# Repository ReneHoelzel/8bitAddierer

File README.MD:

# 8bit Addierer

Das Projekt wurde in Zusammenarbeit mit dem Zuseum in Bautzen entwickelt und soll Schülern und interessierten die Rechenweise eine Computers anhand eines Bytes (=8bit) veranschaulichen. 

## Aufbau

Im unteren Bereich befindet sich ein Arduino Nano V3 als Steuereinheit sowie 8x Doppelpins an die je ein Taster angeschlossen werden kann. Ein Anschlus für den neunten Taster (Erläterung siehe Funktion) befindet sich unter dem Arduino.<br/>

## Funktion

Mit den 8 Tastern kann die dazugehörige 7-Segment Anzeige/rote LED jeweils ein- oder ausgeschalten werden. Je nachdem welche "Bits" eingeschalten sind wird oben in der 3-stelligen Anzeige der entsprechende Wert als Ganzzahl (Byte) ausgegeben.

Zum Beispiel: 0 0 0 0 1 0 0 1 entspricht dem Wert 9.

Mit dem neunten Taster kann das Ergebnis "ausgeblendet" werden (es wird der Wert 999 angezeigt). Dies kann verwendet werden, um einen Wert einzustellen und die Schüler herausfinden zu lassen welcher Byte-Wert sich dahinter verbirgt.

<br/>

<span style="color:red;">Die Verwendung erfolgt auf eigene Gefahr.<span/>

Zum Arduino Programm geht es [hier](https://github.com/ReneHoelzel/8bitAddierer/tree/main/Program).

Es gibt aktuell 2 Board Revisionen:

- [Revision A](8BitZahlAnzeige_RevA/README.MD)

- [Revision B](8BitZahlAnzeige_RevB/README.MD)

Der Unterschied zu beiden Versionen ist, dass bei Revision B die 8x 7-Segment Anzeige und der MAX7219 Steuerchip die Positionen getauscht haben.

## ToDo

- Gehäuse entwerfen

- Animation der 3-stelligen Anzeige, wenn der neunte Taster gedrückt ist.

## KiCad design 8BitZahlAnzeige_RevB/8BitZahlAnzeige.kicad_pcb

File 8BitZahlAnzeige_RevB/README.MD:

# 8bit Addierer

##### Revision B

[Zurück zur Startseite](https://github.com/ReneHoelzel/8bitAddierer/tree/main)

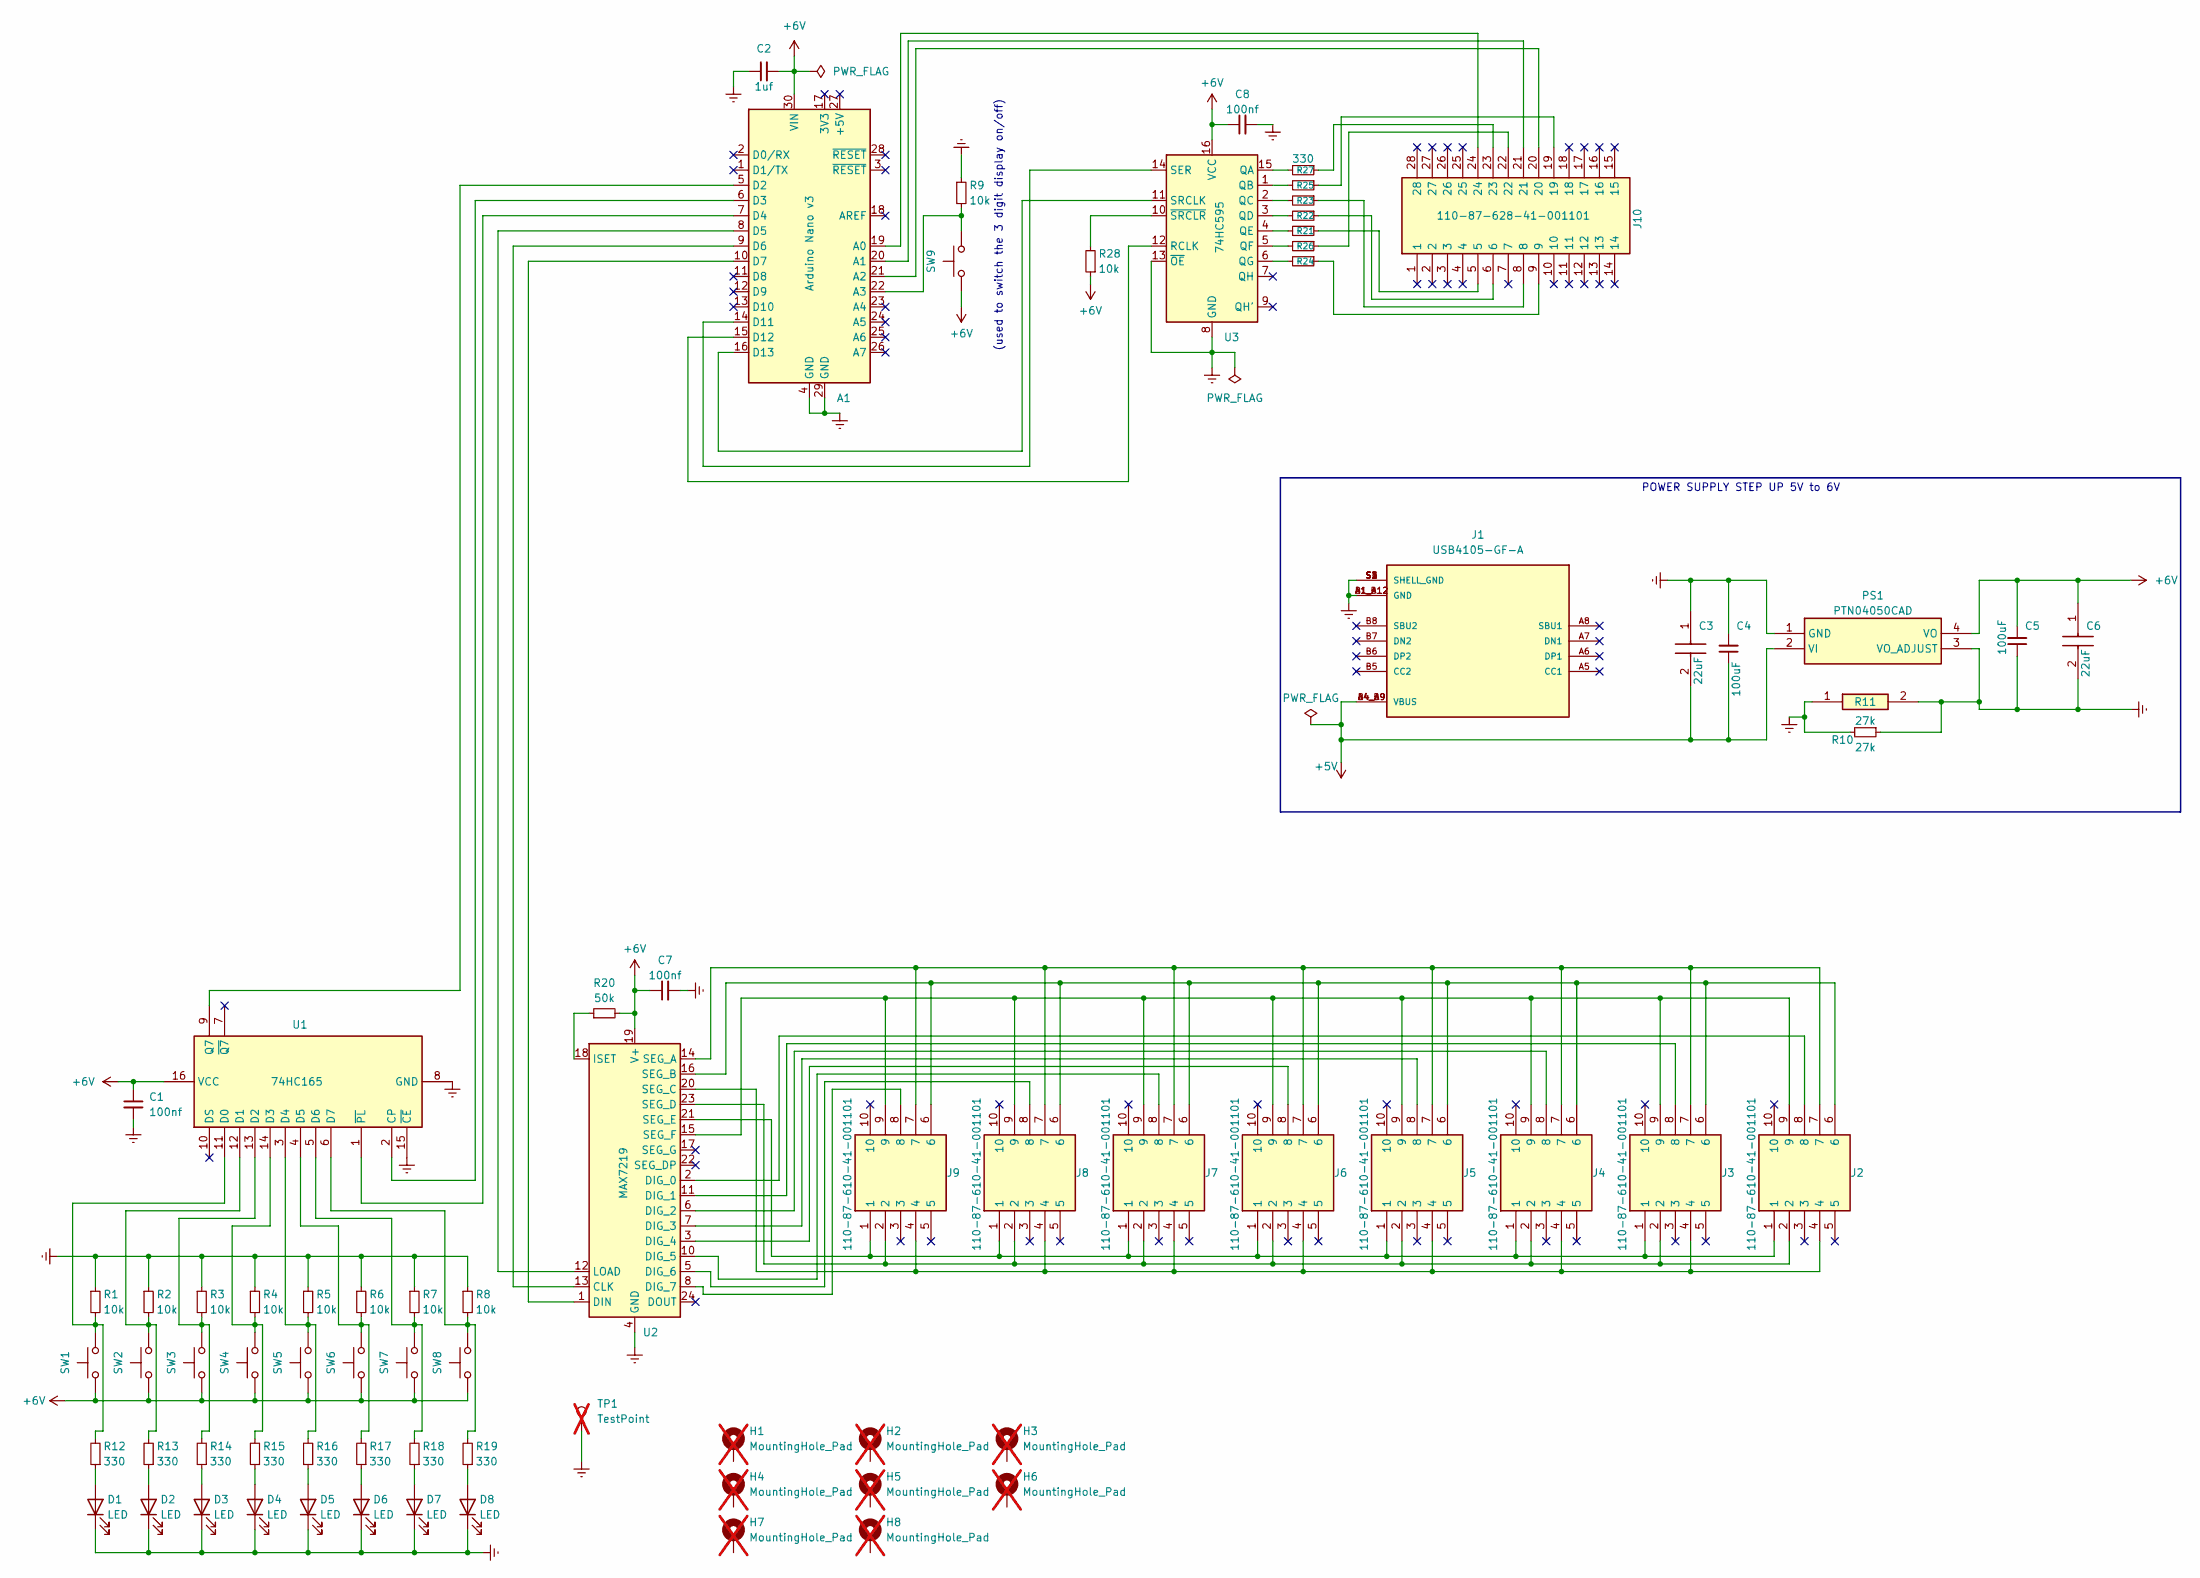
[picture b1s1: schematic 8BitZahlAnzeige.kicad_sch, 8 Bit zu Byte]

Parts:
A1: Arduino Nano v3; Arduino_Nano
C1, C7, C8: 100nf; C_Disc_D5.0mm_W2.5mm_P2.50mm
C2: 1uf; CP_Radial_D4.0mm_P2.00mm
C3, C6: 22uF; C4532_Commercial; Mouser Part Number 810-C4532X7R1C226M10
C4, C5: 100uF; CP_Radial_D5.0mm_P2.50mm
D1, D2, D3, D4, D5, D6, D7, D8: LED; LED_D5.0mm
H1, H2, H3, H4, H5, H6, H7, H8: MountingHole_Pad; MountingHole_3.2mm_M3_DIN965_Pad; not fitted
J1: USB4105-GF-A; GCT_USB4105-GF-A; PARTREV A3
J2, J3, J4, J5, J6, J7, J8, J9: 110-87-610-41-001101; DIPS1524W50P254L1270H370Q10N; Mouser Part Number 437-1108761041001101
J10: 110-87-628-41-001101; DIP-28_W15.24mm_Socket; Mouser Part Number 437-1108762841001101
PS1: PTN04050CAD; PTN04050CAH; Manufacturer_Part_Number PTN04050CAD; Mouser Part Number 595-PTN04050CAD
R1, R2, R3, R4, R5, R6, R7, R8, R9, R28: 10k; R_Axial_DIN0207_L6.3mm_D2.5mm_P10.16mm_Horizontal
R10: 27k; R_Axial_DIN0207_L6.3mm_D2.5mm_P10.16mm_Horizontal
R11: 27k; R_0201_0603Metric; Mouser Part Number 660-RK73H1HTTC2702F
R12, R13, R14, R15, R16, R17, R18, R19, R21, R22, R23, R24, R25, R26, R27: 330; R_Axial_DIN0207_L6.3mm_D2.5mm_P10.16mm_Horizontal
R20: 50k; R_Axial_DIN0207_L6.3mm_D2.5mm_P10.16mm_Horizontal
SW1, SW2, SW3, SW4, SW5, SW6, SW7, SW8, SW9: SW_Push; PinHeader_1x02_P2.54mm_Vertical
TP1: TestPoint; TestPoint_Pad_2.0x2.0mm; not fitted
U1: 74HC165; DIP-16_W7.62mm_Socket
U2: MAX7219; DIP-24_W7.62mm_Socket
U3: 74HC595; DIP-16_W7.62mm_Socket

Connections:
+5V: C3.2, C4.1, J1.A4_B9 (VBUS), J1.B4_A9 (VBUS), PS1.2 (VI)
+6V: A1.30 (VIN), C1.1, C2.2, C5.2, C6.1, C7.1, C8.1, PS1.4 (VO), R20.2, R28.1, SW1.1, SW2.1, SW3.1, SW4.1, SW5.1, SW6.1, SW7.1, SW8.1, SW9.1, U1.16 (VCC), U2.19 (V+), U3.16 (VCC)
GNDREF: A1.4 (GND), A1.29 (GND), C1.2, C2.1, C3.1, C4.2, C5.1, C6.2, C7.2, C8.2, D1.1 (K), D2.1 (K), D3.1 (K), D4.1 (K), D5.1 (K), D6.1 (K), D7.1 (K), D8.1 (K), J1.A1_B12 (GND), J1.B1_A12 (GND), J1.S1 (SHELL_GND), J1.S2 (SHELL_GND), J1.S3 (SHELL_GND), J1.S4 (SHELL_GND), PS1.1 (GND), PS1.3 (VO_ADJUST), R1.1, R2.1, R3.1, R4.1, R5.1, R6.1, R7.1, R8.1, R9.1, R10.1, R10.2, R11.1, R11.2, TP1.1, U1.8 (GND), U1.15 (~CE), U2.4 (GND), U2.9 (GND), U3.8 (GND), U3.13 (~OE)
unnamed: A1.19 (A0), J10.24
unnamed: A1.20 (A1), J10.21
unnamed: A1.21 (A2), J10.20
unnamed: A1.22 (A3), R9.2, SW9.2
unnamed: A1.5 (D2), U1.9 (Q7)
unnamed: A1.6 (D3), U1.2 (CP)
unnamed: A1.7 (D4), U1.1 (~PL)
unnamed: A1.8 (D5), U2.12 (LOAD)
unnamed: A1.9 (D6), U2.13 (CLK)
unnamed: A1.10 (D7), U2.1 (DIN)
unnamed: A1.14 (D11), U3.14 (SER)
unnamed: A1.15 (D12), U3.12 (RCLK)
unnamed: A1.16 (D13), U3.11 (SRCLK)
unnamed: D1.2 (A), R12.1
unnamed: D2.2 (A), R13.1
unnamed: D3.2 (A), R14.1
unnamed: D4.2 (A), R15.1
unnamed: D5.2 (A), R16.1
unnamed: D6.2 (A), R17.1
unnamed: D7.2 (A), R18.1
unnamed: D8.2 (A), R19.1
unnamed: J10.5, R21.1
unnamed: J10.6, R22.1
unnamed: J10.8, R23.1
unnamed: J10.9, R24.1
unnamed: J10.19, R25.1
unnamed: J10.22, R26.1
unnamed: J10.23, R27.1
unnamed: R1.2, R12.2, SW1.2, U1.11 (D0)
unnamed: R2.2, R13.2, SW2.2, U1.12 (D1)
unnamed: R3.2, R14.2, SW3.2, U1.13 (D2)
unnamed: R4.2, R15.2, SW4.2, U1.14 (D3)
unnamed: R5.2, R16.2, SW5.2, U1.3 (D4)
unnamed: R6.2, R17.2, SW6.2, U1.4 (D5)
unnamed: R7.2, R18.2, SW7.2, U1.5 (D6)
unnamed: R8.2, R19.2, SW8.2, U1.6 (D7)
unnamed: J2.8, U2.2 (DIG_0)
unnamed: J3.8, U2.11 (DIG_1)
unnamed: J4.8, U2.6 (DIG_2)
unnamed: J5.8, U2.7 (DIG_3)
unnamed: J6.8, U2.3 (DIG_4)
unnamed: J7.8, U2.10 (DIG_5)
unnamed: J8.8, U2.5 (DIG_6)
unnamed: J9.8, U2.8 (DIG_7)
unnamed: R20.1, U2.18 (ISET)
unnamed: J2.7, J3.7, J4.7, J5.7, J6.7, J7.7, J8.7, J9.7, U2.14 (SEG_A)
unnamed: J2.6, J3.6, J4.6, J5.6, J6.6, J7.6, J8.6, J9.6, U2.16 (SEG_B)
unnamed: J2.4, J3.4, J4.4, J5.4, J6.4, J7.4, J8.4, J9.4, U2.20 (SEG_C)
unnamed: J2.2, J3.2, J4.2, J5.2, J6.2, J7.2, J8.2, J9.2, U2.23 (SEG_D)
unnamed: J2.1, J3.1, J4.1, J5.1, J6.1, J7.1, J8.1, J9.1, U2.21 (SEG_E)
unnamed: J2.9, J3.9, J4.9, J5.9, J6.9, J7.9, J8.9, J9.9, U2.15 (SEG_F)
unnamed: R27.2, U3.15 (QA)
unnamed: R25.2, U3.1 (QB)
unnamed: R23.2, U3.2 (QC)
unnamed: R22.2, U3.3 (QD)
unnamed: R21.2, U3.4 (QE)
unnamed: R26.2, U3.5 (QF)
unnamed: R24.2, U3.6 (QG)
unnamed: R28.2, U3.10 (~SRCLR)

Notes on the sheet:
(used to switch the 3 digit display on/off)
POWER SUPPLY STEP UP 5V to 6V

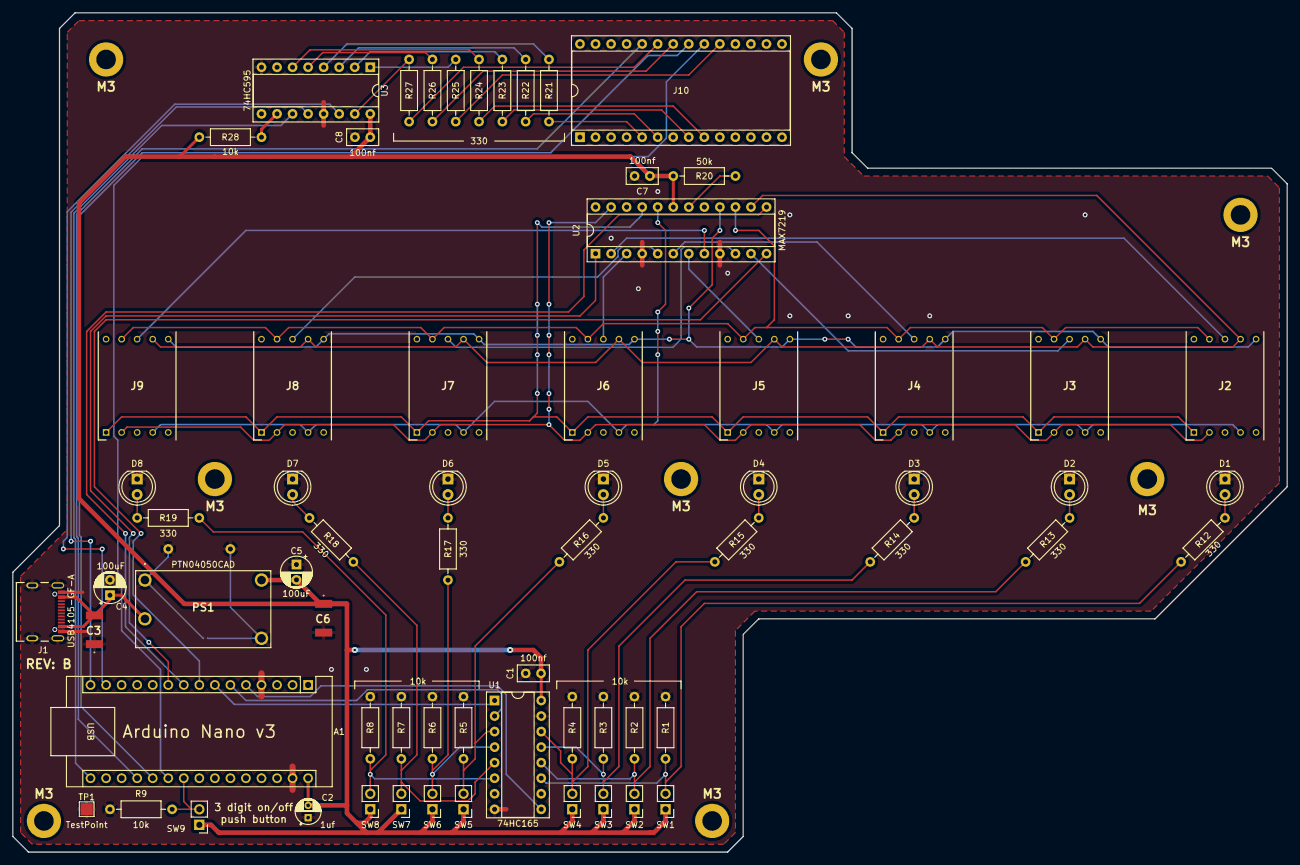
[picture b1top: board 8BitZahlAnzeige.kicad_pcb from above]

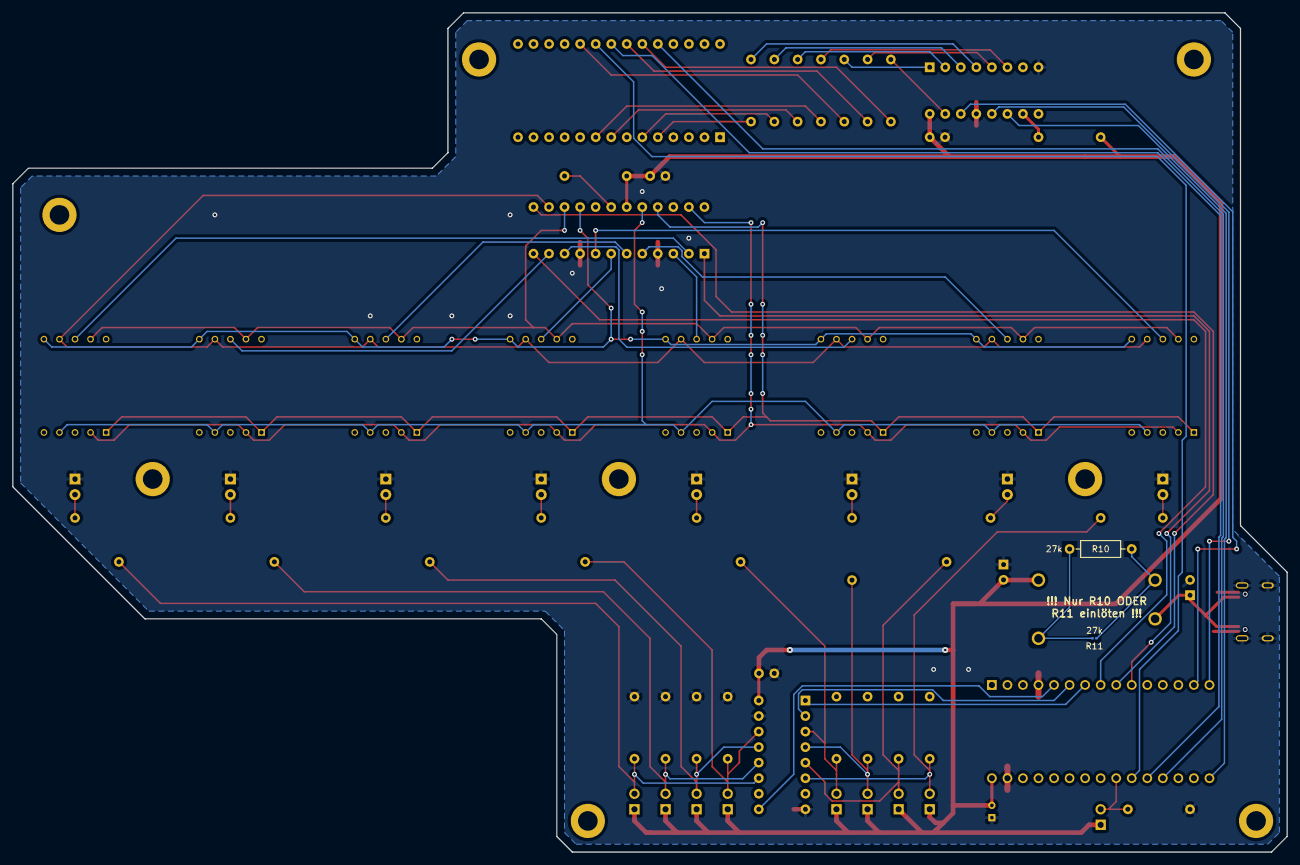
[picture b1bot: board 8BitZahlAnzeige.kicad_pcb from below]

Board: 2 copper layers, 208.3 x 137.2 mm, 77 parts (2 on the bottom side), 62 nets.

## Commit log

2023-10-29 Initial Upload
2023-10-29 Bilder und Readme's aktualisiert
2023-10-29 - Ignorieren automatisch generierter Backup-Ordner - Anpassen der Leitungen im Rev B Layout
2023-10-29 Readme angepasst
